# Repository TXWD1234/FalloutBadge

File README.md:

# **FalloutBadge**
A personal badge card PCB made during the evert of [Fallout](https://fallout.hackclub.com).

# Project Description
A simple half-adder circuit that calculate the result from addition of 2 one bit number.
The main challange in this project is to implement the logic gates, and use them to compose the adder.

# Logic Description
The adder have 2 input pins and 2 output pins:
- input: first adder number
- input: second adder number
- output: result (the value for the original digit)
  - this is a XOR gate
- output: carry (the additional result for the next digit)
  - this is an AND gate

# Gallery
***AND gate:***

***XOR gate:***

***ADD circuit:***

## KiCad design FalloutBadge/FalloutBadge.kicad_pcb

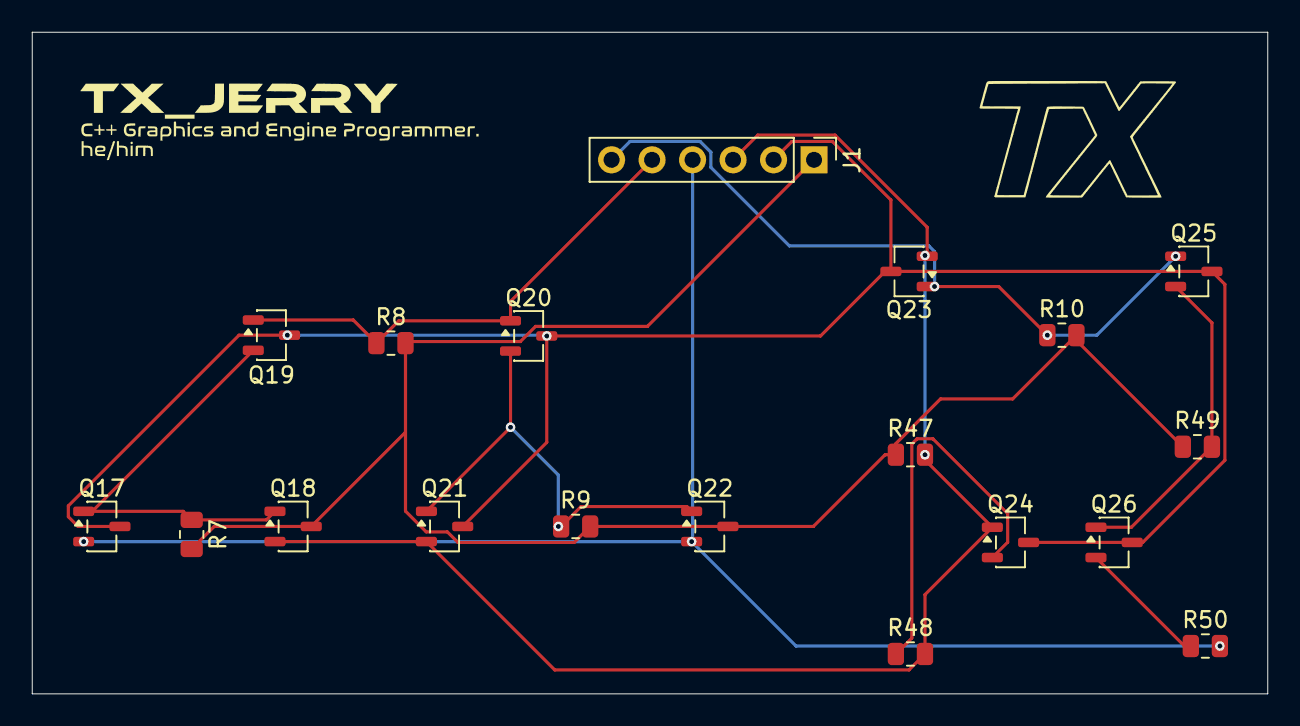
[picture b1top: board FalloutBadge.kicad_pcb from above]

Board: 2 copper layers, 77.5 x 41.5 mm, 19 parts (0 on the bottom side), 11 nets.

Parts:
J1: Conn_01x06_Pin; PinHeader_1x06_P2.54mm_Vertical
Q17, Q18, Q19, Q20, Q21, Q22, Q23, Q24, Q25, Q26: Q_NMOS_DGS; SOT-23-3
R7, R8, R9, R10, R47, R48, R49, R50: 10k; R_0805_2012Metric

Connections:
/CARRY: J1.6, Q23.1 (D), Q25.1 (D), R10.1
/GND: J1.2, Q17.3 (S), Q19.3 (S), Q20.3 (S), Q21.3 (S), Q23.3 (S), Q24.3 (S), Q25.3 (S), Q26.3 (S)
/IN_1: J1.3, Q18.2 (G), Q21.2 (G), Q23.2 (G), Q24.1 (D), R47.2, R48.2
/IN_2: J1.4, Q17.2 (G), Q22.2 (G), R50.2
/RESULT: J1.5, Q19.1 (D), Q20.1 (D), R8.1
/VCC: J1.1, Q18.3 (S), Q22.3 (S), R7.2, R8.2, R9.2, R10.2, R47.1, R49.1
unnamed: Q17.1 (D), Q18.1 (D), Q19.2 (G), R7.1
unnamed: Q20.2 (G), Q21.1 (D), Q22.1 (D), R9.1
unnamed: Q24.2 (G), R48.1
unnamed: Q25.2 (G), Q26.1 (D), R49.2
unnamed: Q26.2 (G), R50.1
